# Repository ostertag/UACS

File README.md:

# UACS
University Access Controll System

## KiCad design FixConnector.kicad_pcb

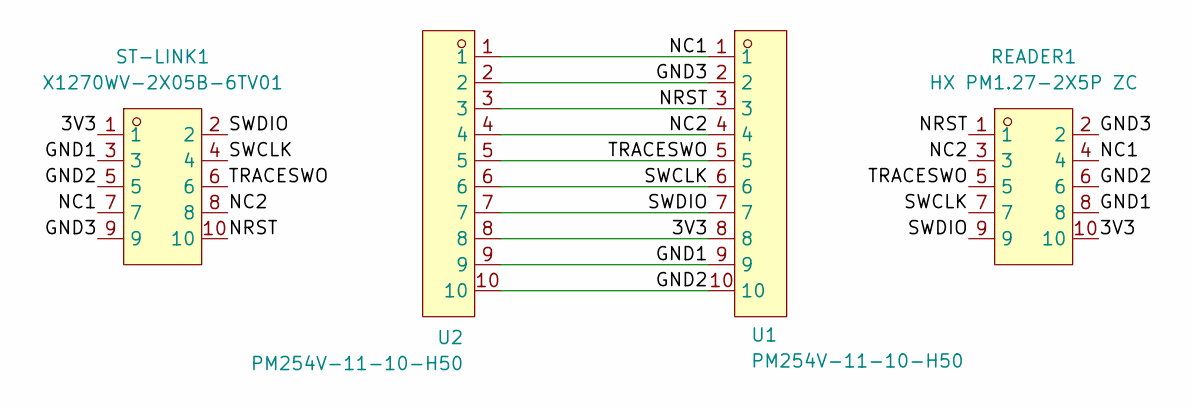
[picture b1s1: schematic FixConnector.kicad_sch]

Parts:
READER1: HX PM1.27-2X5P ZC; HDR-TH_10P-P1.27-V-F-R2-C5-S1.27; MPN HX PM1.27-2x5P ZC; LCSC Part C22438129
ST-LINK1: X1270WV-2X05B-6TV01; IDC-TH_10P-P1.27-X1270WV-2X05A-6TV01; MPN X1270WV-2x05B-9TV01; LCSC Part C2962225
U1, U2: PM254V-11-10-H50; HDR-TH_10P-P2.54-V-F-4; MPN PM254V-11-10-H50; LCSC Part C55218824

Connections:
/3V3: READER1.10, ST-LINK1.1, U1.8, U2.8
/GND1: READER1.8, ST-LINK1.3, U1.9, U2.9
/GND2: READER1.6, ST-LINK1.5, U1.10, U2.10
/GND3: READER1.2, ST-LINK1.9, U1.2, U2.2
/NC1: READER1.4, ST-LINK1.7, U1.1, U2.1
/NC2: READER1.3, ST-LINK1.8, U1.4, U2.4
/NRST: READER1.1, ST-LINK1.10, U1.3, U2.3
/SWCLK: READER1.7, ST-LINK1.4, U1.6, U2.6
/SWDIO: READER1.9, ST-LINK1.2, U1.7, U2.7
/TRACESWO: READER1.5, ST-LINK1.6, U1.5, U2.5

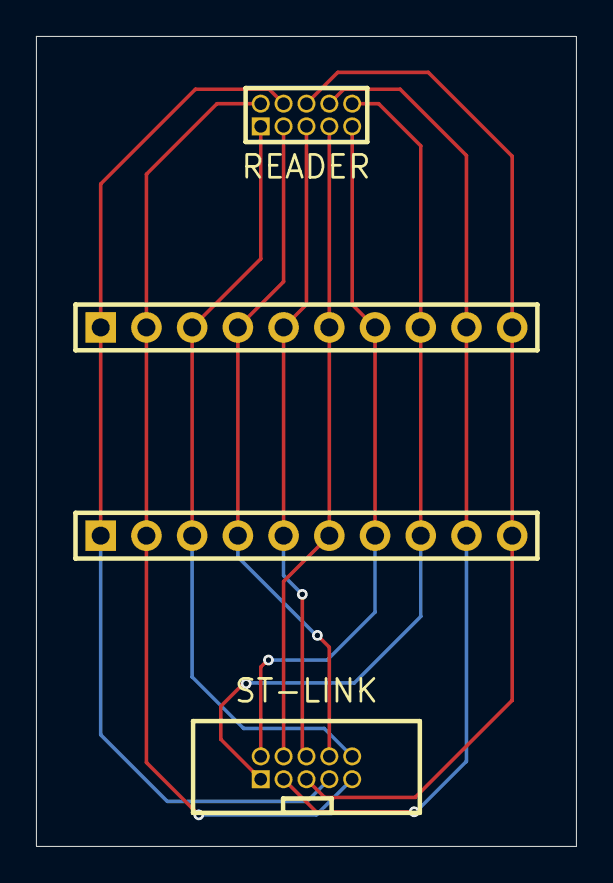
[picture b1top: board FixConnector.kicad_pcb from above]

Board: 2 copper layers, 30.0 x 45.0 mm, 4 parts (0 on the bottom side), 10 nets.

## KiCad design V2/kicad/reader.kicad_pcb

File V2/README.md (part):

# Chapter 1 — System Overview

## Project: UACS (RFID Audio CAN Node)

**Repository:** https://github.com/ostertag/UACS  
**Microcontroller:** STM32H523CET6 (Arm Cortex-M33, LQFP-48)  
**EDA tools:** KiCad (schematic + PCB), STM32CubeMX (pin/peripheral assignment)  
**Debug hardware:** STLINK-V3PWR  
**Component sourcing:** LCSC / JLCPCB

## Introduction

UACS is a custom-designed printed circuit board that integrates contactless RFID reading, audio feedback through a loudspeaker, CAN FD communication, and SD-card audio storage, built around an STM32H523CET6 microcontroller. The board communicates over a CAN FD link, carried over standard RJ45/Cat5 cabling, to a host computer (a Raspberry Pi).

The STM32H523xx is a high-performance microcontroller built on the Arm Cortex-M33 32-bit core, operating at up to 250 MHz, with a single-precision FPU and TrustZone security extension. *[1]*

## System Architecture

The system is a single-board reader node whose main functional blocks are:

- **Microcontroller** — STM32H523CET6 (Cortex-M33, 250 MHz, LQFP-48), central coordinator of all peripherals.
- **RFID reader** — RC522 module (NXP MFRC522), reads ISO/IEC 14443 A / MIFARE cards and tags over SPI.
- **Audio amplifier** — MAX98357A, digital Class D amplifier with I²S input; drives the loudspeaker directly.
- **SD card** — micro-SD slot for audio file storage, connected over SPI.
- **CAN FD transceiver** — TCAN1057A, links the board to the host over Cat5/RJ45 cabling.
- **Power supply** — dual 5 V input (USB-C and RJ45), stepped down to 3.3 V by an MCP16301H buck converter.
- **USB-C interface** — USB 2.0 full-speed device, used for firmware flashing (DFU) and debugging.
- **Indicator LEDs** — two dual-colour (red/green) SMD LEDs for user feedback.

## Scope and Goal of This Work

This work continues the UACS project previously developed in the Deadlock project series. *[predecessor]* The principal goal is a thoroughly documented hardware design that can be reliably reproduced. In particular:

- **Reproducibility** — every component value is either calculated from first principles or traced to a specific datasheet reference, so the design can be rebuilt without reliance on undocumented institutional knowledge.
- **Availability** — components are sourced from LCSC/JLCPCB and selected for availability, good documentation, and competitive cost.
- **Robustness** — the dual power input, remote reset, and remote bootloader-entry capability allow firmware updates and recovery without physical access to a deployed board.

> **Note on references.** Inline citations use italic bracketed numbers, e.g.  *[1]*, referring to the numbered list at the end of the document. References 1–11 are component datasheets; 12–23 are technical literature.

---

# Chapter 2 — Design and Assembly of the UACS PCB

The UACS reader is a printed circuit board on which an STM32H523CET6 microcontroller, an RFID front-end module, an I²S audio amplifier, a micro-SD slot, a CAN FD transceiver, and associated connectors are assembled. User feedback is provided by two dual-colour LEDs. The board can be powered either from a USB-C connector or from the RJ45 CAN cable.

## 2.1 Microcontroller — STM32H523CET6

The STM32H523CET6 is the central controller of the board. It is supplied in an LQFP-48 package and runs the Cortex-M33 core at 250 MHz. *[1]* All peripheral communication — SPI, I²S, FDCAN, and USB — is handled by this device.

### 2.1.1 Debug Interface (SWD)

The board exposes a 10-pin 1.27 mm-pitch Cortex debug connector (SWD1), driven by an STLINK-V3PWR probe.

The STM32H523 supports both JTAG and Serial Wire Debug (SWD), as well as the Embedded Trace Macrocell (ETM). *[1]* SWD was selected over JTAG because it reduces the debug interface to two active signals — SWDIO and SWCLK — while providing equivalent core-debug and memory-access capability to the higher-pin-count JTAG interface. *[12][13]* On a pin-constrained LQFP-48 device, freeing the JTAG pins (TDI, TDO, nTRST) for other functions is a meaningful saving, and SWD is the conventional default for Cortex-M bring-up. *[13]*

The Serial Wire Output trace pin (TRACESWO) is brought out on PB3, enabling single-wire instrumentation trace (printf-style debug output) without consuming a UART peripheral. The connector follows the standard 10-pin 1.27 mm Cortex-debug pinout, which balances size against reliability. *[13]*

The STLINK-V3PWR probe as we already had it available. *[4]*

### 2.1.2 Reset Circuit

The NRST line is shared between three reset sources: the on-board push button (RESET1), the remote reset line carried over the RJ45 connector (Section 2.4.2), and the STLINK debug probe. If software reset over SWD fails, the probe can still assert NRST to force a hardware reset. *[13]*

#### Resistor R5

A 10 kΩ pull-up resistor holds the NRST line high during normal operation. Without it the line would float and could trigger spurious resets from noise.

#### Capacitor C3

A 100 nF capacitor from NRST to GND provides debounce for the mechanical reset button and protection against parasitic resets. ST explicitly recommends an external capacitor on NRST for exactly this purpose. *[1]*

### 2.1.3 BOOT0 Circuit

BOOT0 selects whether the MCU starts from user flash (normal operation) or from the embedded system bootloader. The STM32H523 embedded bootloader, located in system memory and programmed by ST during production, can reprogram the flash over USART, I²C, I³C, SPI, FDCAN, or USB-FS (via DFU). *[1]* On UACS, USB-FS DFU is the relevant path (Section 2.6).

BOOT0 is additionally exposed on the RJ45 connector (Section 2.4.2), so the bootloader can be entered remotely without physical access to the board.

#### Resistor R6

A 10 kΩ pull-down resistor holds BOOT0 low during normal operation. With BOOT0 low, the device boots from user flash at address 0x0800 0000. *[1]*

#### Resistor R7

A 10 kΩ series resistor is placed between the R6 junction and the BOOT1 switch to limit current and provide isolation between the pull-down and the switch.

#### Switch BOOT1

An SPDT switch that selects GND (normal boot) or 3.3 V (bootloader entry). Connecting BOOT0 to 3.3 V causes the MCU to enter the embedded system bootloader on the next reset.

### 2.1.4 Crystal Oscillator

A 16 MHz crystal (Y1, SMD3225-4P, 10 pF load) provides the high-speed external (HSE) clock. The STM32H523 supports a 4–50 MHz HSE oscillator. *[1]* Although the device has an internal 64 MHz HSI oscillator, an external crystal is used because the USB and CAN peripherals require a more accurate and stable time base than the internal RC oscillator can guarantee. The USB full-speed interface has particularly tight frequency-tolerance requirements.

No 32.768 kHz crystal is fitted; the LSE pins (PC14/PC15) are left unconnected and configured in Analog mode.

#### Capacitors C1 and C2

Per the AN2867 oscillator load model *[24]*, the two external capacitors $C_{L1}$ and $C_{L2}$ together with PCB stray capacitance $C_S$ must equal the crystal's specified load $C_L$:

$$C_L = \frac{C_{L1} \cdot C_{L2}}{C_{L1} + C_{L2}} + C_S$$

Placing identical capacitors on both sides ($C_{L1} = C_{L2} = C$) simplifies this to $C = 2(C_L - C_S)$. With $C_L = 10\,\text{pF}$ and $C_S = 5\,\text{pF}$ (AN2867 typical range: 2–7 pF):

$$C = 2\,(10 - 5) = 10\,\text{pF}$$

Two 10 pF C0G capacitors are therefore placed to GND, one on each side of the crystal. C0G (Class 1) dielectric is used because its capacitance is essentially independent of temperature and applied voltage — typically within ±30 ppm/°C — which is important for a stable oscillator load. *[19][20]*

### 2.1.5 VCAP — Internal Regulator Capacitors

The STM32H5 family integrates an LDO voltage regulator (nominally 3.3 V → 1.2 V core) that requires external stabilisation capacitors on its VCAP pin(s). *[1]* The datasheet specifies this requirement explicitly in Section 5.3.2, "VCAP external capacitor". *[1]*

#### Capacitors C14 and C15

Two 2.2 µF capacitors, one per VCAP pin, are placed to GND. These are mandated by the datasheet for the internal regulator's stability and are not interchangeable with generic decoupling — the value and placement are part of the regulator's stability requirement.

### 2.1.6 Power Pins and Decoupling

The STM32H523 uses several supply domains: the main VDD digital supply, an analog supply (VDDA), a USB supply domain, and the VBAT backup domain. *[1]*

- **VDD** — supplied from +3.3 V; decoupled with C8–C11 (100 nF each) for high-frequency bypass, plus C12 (10 µF) for bulk capacitance.
- **VDDA** — analog supply, filtered from the 3.3 V rail through the VDDA filter (Section 2.3.3).
- **VBAT** — tied to the 3.3 V rail, since no backup battery is used.
- **VSS / VSSA** — ground.

### 2.1.7 RFID Reader — RC522 Module (MFRC522)

The RFID front end is an RC522 module based on the NXP MFRC522 IC, mounted on an 8-pin 2.54 mm socket (RC1) and connected to the MCU over SPI.

The RC522 module was selected because it was used in the predecessor project, allowing existing experience and firmware to be carried over. The MFRC522 is a 13.56 MHz reader/writer IC supporting the ISO/IEC 14443 A / MIFARE protocol family — MIFARE Mini, 1K, 4K, Ultralight, DESFire EV1, MIFARE Plus, and NTAG — with a host SPI interface running up to 10 Mbit/s. *[3]*

**Interface signals:**

- **SPI** — shares SPI1 with the SD card (Section 2.2); chip select is software-controlled on PB14 (RFID_SS), active low.
- **RST (PB10)** — the MCU drives the module's NRSTPD pin as a push-pull output. The pin defaults high at boot so the reader starts in normal operation; driving it low triggers a hard reset/power-down of the module. *[3]*
- **IRQ (PB13)** — the module's interrupt output drives EXTI13, configured for falling-edge interrupts, enabling interrupt-driven card detection rather than polling.

On the MFRC522, the IRQ pin is open-drain and active-low by default, *[3]* which matches the MCU's falling-edge EXTI configuration; only an MCU-side internal pull-up is required on PB13, with no external resistor. The MFRC522's CommIEnReg register must be configured in firmware to enable interrupt propagation to the IRQ pin. *[3]*

#### Capacitor C21

A 10 µF local bypass capacitor is placed on the module VCC pin. VCC connects directly to the 3.3 V rail. (PB12 is left unconnected; an earlier plan to use it for switched module power was dropped, since a single GPIO cannot source the MFRC522's worst-case current.)

---

## 2.2 SD Card — MLD-TF PUSH-H18

The micro-SD slot (U3) stores the audio files played back through the amplifier.

SPI was chosen over SDMMC for three reasons: the application does not require SDMMC's higher throughput; SPI was already in use for the RFID reader, reducing the number of active interfaces and occupied pins; and while this STM32 series supports SDMMC, it is only available on larger packages.

The SD card shares SPI1 with the RC522 reader, with its own software chip select on PB0 (SD_SS). In SPI mode, the card's CD/DAT3 pin (slot pin 2) functions as the active-low chip select; this is confirmed by the slot's pin table, which labels pin 2 as CD/DAT3 with I/O type PP. *[8]*

The MLD-TF PUSH-H18 uses a push-push ejection mechanism (card ejects on the second press); the card-detect switch is a separate mechanical contact from the signal pins. *[8]*

#### Card Detect — PB1

The slot's dedicated card-detect mechanical contact drives PB1 (SD_DETECTED) as a GPIO input, allowing the firmware to detect card insertion and removal.

#### Resistors R2 and R3

Two 10 kΩ pull-up resistors are placed to 3.3 V on the DAT1 line (R2) and the DAT2 line (R3). In SPI mode both of these data lines are unused; the pull-ups keep them at a defined high level rather than floating.

---

## 2.3 Power Supply

### 2.3.1 Architecture

The board accepts power from two independent 5 V sources, diode-OR-ed onto a common +5 V rail and then stepped down to 3.3 V by a buck converter.

| Source | OR-ing diode | ESD protection |
|--------|--------------|----------------|
| USB-C VBUS | D8 (PMEG2010ER) | D7 (PESD5V0U1BA,115) |
| RJ45 pair (brown) | D1 (PMEG2010ER) | D2 (PESD5V0U1BA,115) |

The two inputs serve different operational scenarios. The RJ45 input is the primary supply during normal deployment, where the board is powered from the CAN cabling infrastructure. The USB-C input is used during development and programming, when the board is connected to a PC without the full CAN harness. Diode OR-ing lets both sources be connected simultaneously without back-feeding. Each TVS diode is placed as close as possible to its respective input connector for effective clamping. *[10]*

### 2.3.2 Buck Converter — MCP16301H

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
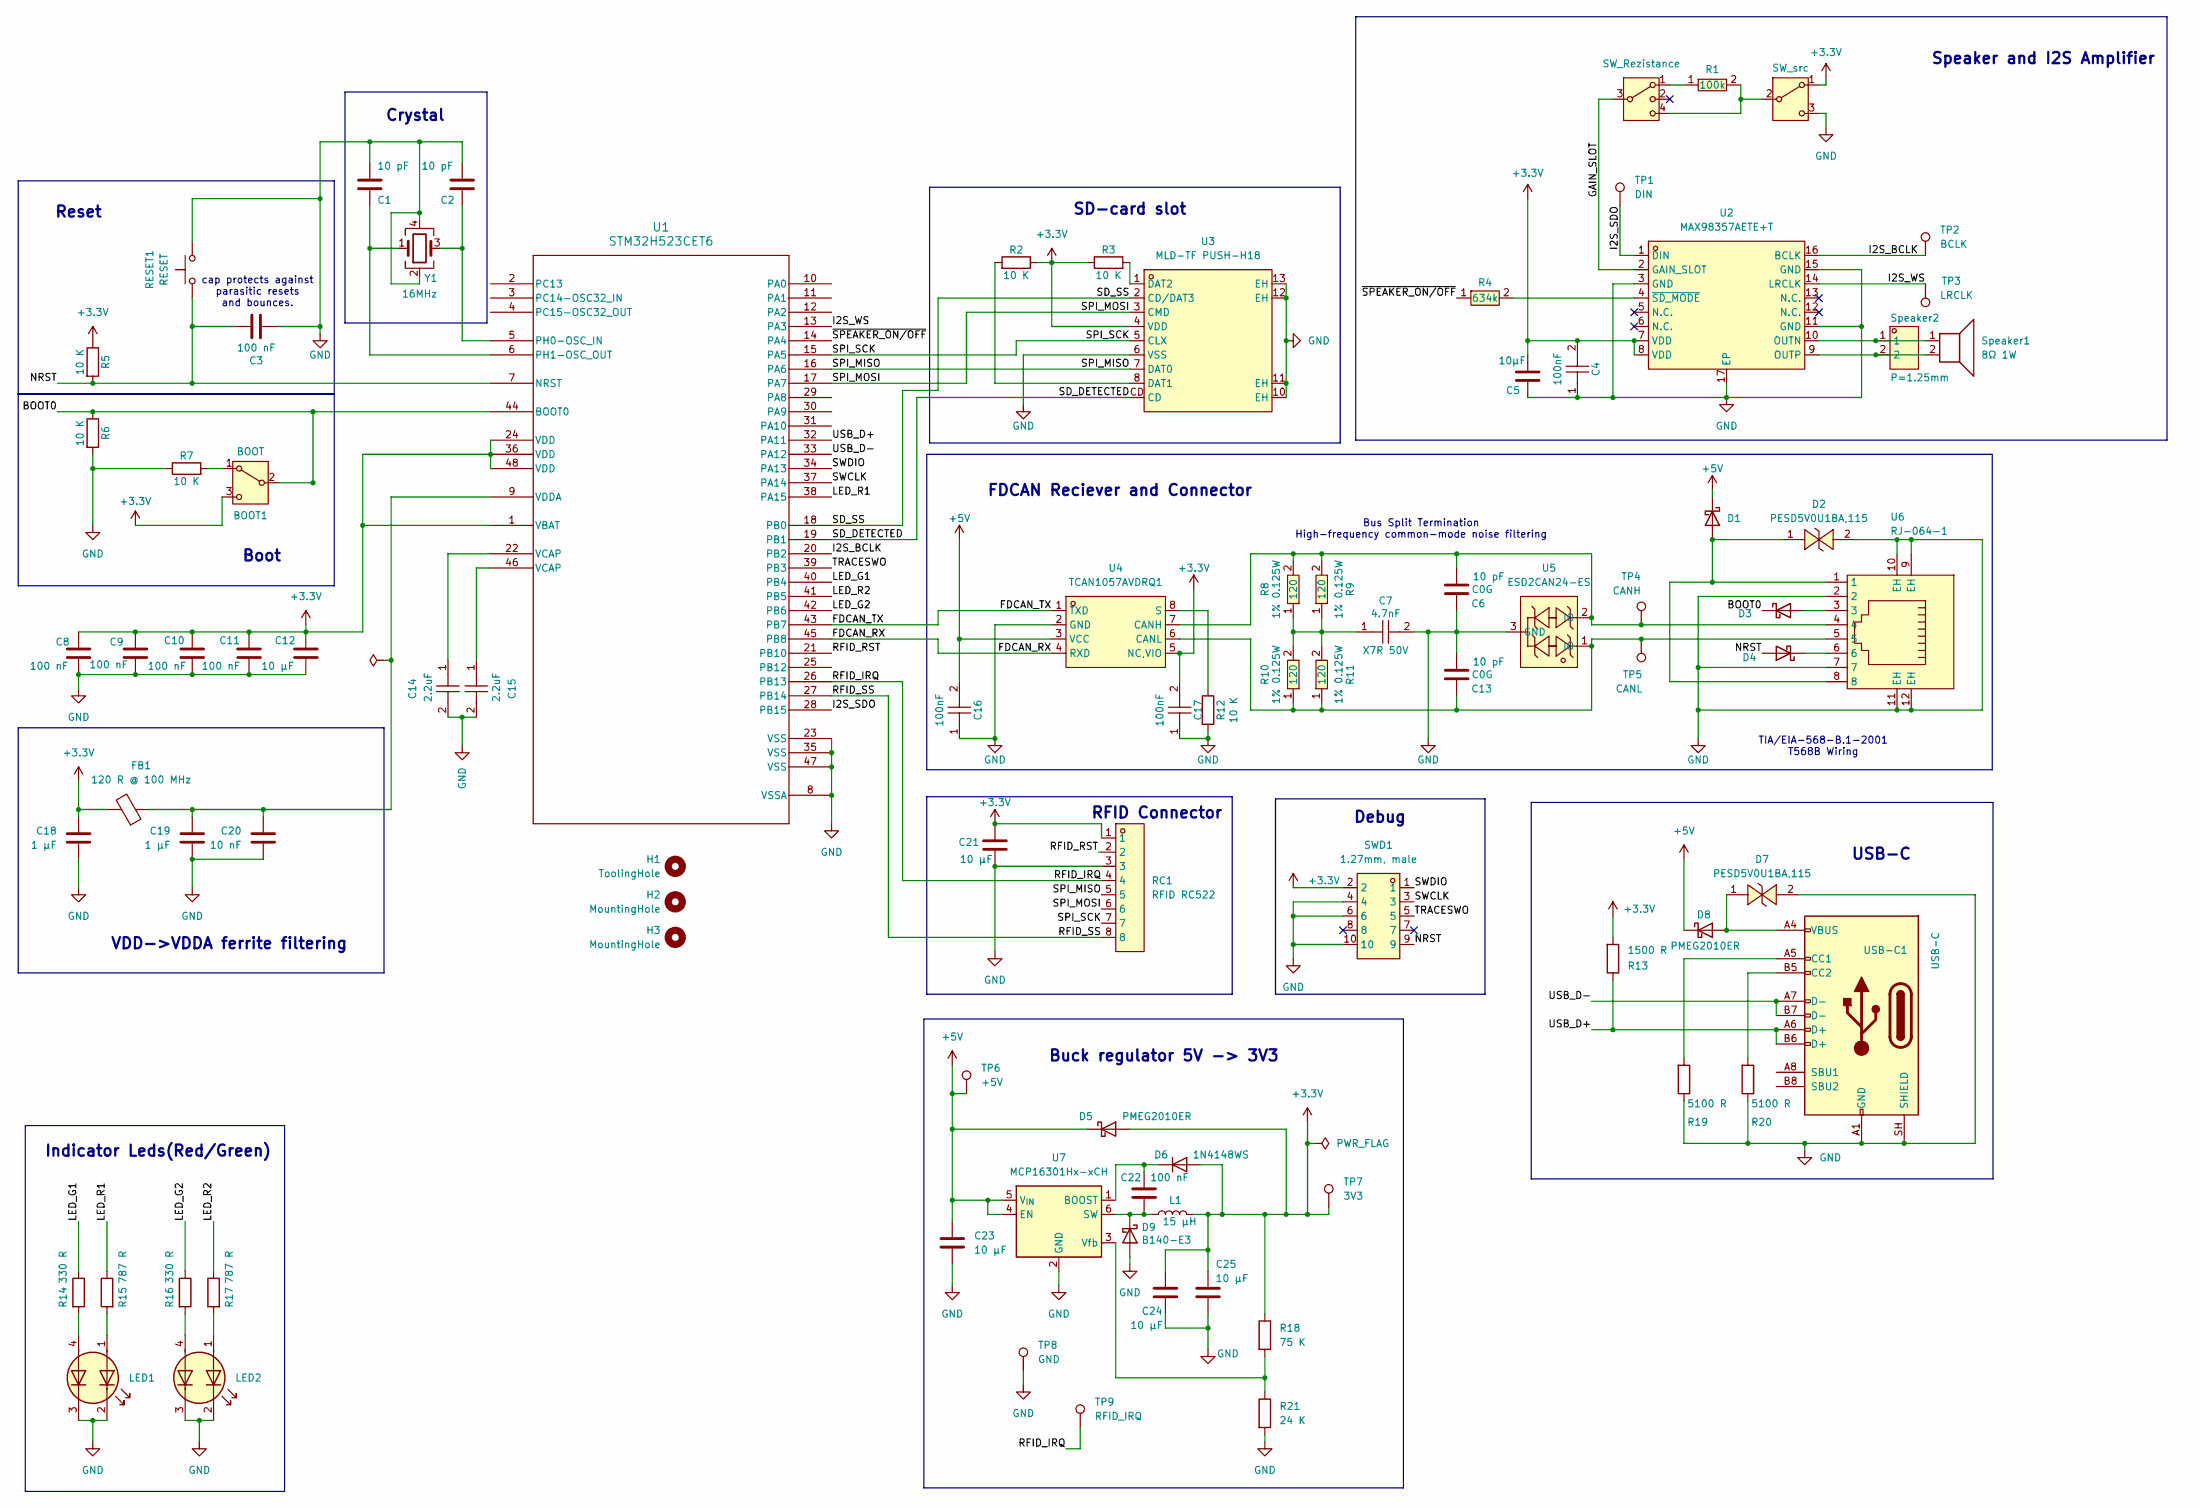
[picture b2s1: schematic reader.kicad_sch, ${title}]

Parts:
BOOT1: BOOT; SW_SPDT_PCM12; LCSC C109335
C1, C2, C6, C13: 10 pF; C_0402_1005Metric; LCSC C32949
C3, C8, C9, C10, C11, C22: 100 nF; C_0402_1005Metric; LCSC C1525
C4, C16, C17: CC0603KRX7R9BB104; C0603; MPN CC0603KRX7R9BB104; LCSC Part C14663
C5: 10µF; C_0603_1608Metric; LCSC C96446
C7: 4.7nF; C0603; MPN CC0603JRX7R9BB472; LCSC Part C115060
C12, C21, C23, C24, C25: 10 µF; C_0603_1608Metric; LCSC C96446
C14, C15: GRM155C80J225KE95D; C0402; MPN GRM155C80J225KE95D; LCSC Part C521077
C18, C19: 1 µF; C_0402_1005Metric; LCSC C52923
C20: 10 nF; C_0402_1005Metric; LCSC C15195
D1, D3, D4, D5, D8: PMEG2010ER; Nexperia_CFP3_SOD-123W; LCSC C82288
D2, D7: PESD5V0U1BA,115; SOD-323_L1.8-W1.3-LS2.5-BI; MPN PESD5V0U1BA,115; LCSC Part C552574
D6: 1N4148WS; D_SOD-323; LCSC C2128
D9: B140-E3; D_SMA; LCSC C968568
FB1: 120 R @ 100 MHz; L_0603_1608Metric; LCSC C2661467
H1: ToolingHole; ToolingHole_1.152mm
H2, H3: MountingHole; ToolingHole_1.152mm
L1: 15 µH; L_Coilcraft_LPS3010; LCSC C520285
LED1, LED2: APHBM2012LSURKZGKC; LED_Kingbright_APHBM2012_2x1.25mm; LCSC C6465979
R1: 0603WAF1003T5E; R0603; MPN 0603WAF1003T5E; LCSC Part C25803
R2, R3, R5, R6, R7, R12: 10 K; R_0603_1608Metric; LCSC C25804
R4: 0805W8F1501T5E; R0805; MPN 0805W8F1501T5E; LCSC Part C4310
R8, R9, R10, R11: 120; R0805; MPN CL0805FN120RP; LCSC Part C17437
R13: 1500 R; R_0402_1005Metric; LCSC C25867
R14, R16: 330 R; R_0402_1005Metric; LCSC C25104
R15, R17: 787 R; R_0402_1005Metric; LCSC C4109
R18: 75 K; R_0603_1608Metric; LCSC C23242
R19, R20: 5100 R; R_0402_1005Metric; LCSC C25905
R21: 24 K; R_0603_1608Metric; LCSC C23352
RC1: RFID RC522; PinSocket_1x08_P2.54mm_Vertical; MPN HX PM2.54-1x8P ZC H11; LCSC Part C41427523
RESET1: RESET; SW_PUSH_6mm; LCSC C2889001
SW1: SW_Rezistance; SW-SMD_SSSS812201; LCSC Part C160878
SW2: SW_src; SW_SPDT_PCM12; LCSC C109335
SWD1: 1.27mm, male; IDC-TH_10P-P1.27-X1270WV-2X05A-6TV01; MPN X1270WV-2x05B-9TV01; LCSC Part C2962225
Speaker1: 8Ω 1W; LCSC C530539
Speaker2: P=1.25mm; CONN-TH_0530470210; MPN 530470210; LCSC Part C114130
TP1: DIN; TestPoint_Drill-1mm
TP2: BCLK; TestPoint_Drill-1mm
TP3: LRCLK; TestPoint_Drill-1mm
TP4: CANH; TestPoint_Drill-1mm
TP5: CANL; TestPoint_Drill-1mm
TP6: +5V; TestPoint_Drill-1mm
TP7: 3V3; TestPoint_Drill-1mm
TP8: GND; TestPoint_Drill-1mm
TP9: RFID_IRQ; TestPoint_Drill-1mm
U1: STM32H523CET6; LQFP48_STM
U2: MAX98357AETE+T; TQFN-16_L3.0-W3.0-P0.50-BL-EP1.5; MPN MAX98357AETE+T; LCSC Part C910544
U3: MLD-TF PUSH-H18; SD-SMD_MLD-TF-PUSH-H18; MPN MLD-TF PUSH-H18; LCSC Part C52750848
U4: TCAN1057AVDRQ1; SOIC-8_L4.9-W3.9-P1.27-LS6.0-BL; MPN TCAN1057AVDRQ1; LCSC Part C3235000
U5: ESD2CAN24-ES; SOT-23-3_L2.9-W1.3-P1.90-LS2.4-BR; MPN ESD2CAN24-ES; LCSC Part C19170841
U6: RJ-064-1; CONN-SMD_RJ-064; MPN RJ-064-1; LCSC Part C7205199
U7: MCP16301Hx-xCH; SOT-23-6; LCSC C511272
USB-C1: USB-C; USB_C_Receptacle_GCT_USB4105-xx-A_16P_TopMnt_Horizontal; LCSC C2765186
Y1: 16MHz; Crystal_SMD_3225-4Pin_3.2x2.5mm; LCSC C13738

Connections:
+3.3V: BOOT1.3 (C), C4.2, C5.2, C8.1, C9.1, C10.1, C11.1, C12.1, C17.2, C18.1, C21.1, C24.1, C25.1, D5.2 (A), D6.2 (A), FB1.2, L1.2, R2.1, R3.1, R5.1, R13.2, R18.1, RC1.1, SW2.1 (A), SWD1.2, TP7.1 (1_1), U1.1 (VBAT), U1.24 (VDD), U1.36 (VDD), U1.48 (VDD), U2.7 (VDD), U2.8 (VDD), U3.4 (VDD), U4.5 (NC,VIO); also elsewhere on the board
+5V: C16.2, C23.1, D1.1 (K), D5.1 (K), D8.1 (K), TP6.1 (1_1), U4.3 (VCC), U7.4 (EN), U7.5 (V_{IN})
/BOOT0: BOOT1.2 (B), D3.1 (K), R6.1, U1.44 (BOOT0)
/FDCAN_RX: U1.45 (PB8), U4.4 (RXD)
/FDCAN_TX: U1.43 (PB7), U4.1 (TXD)
/GAIN_SLOT: SW1.3, U2.2 (GAIN_SLOT)
/I2S_BCLK: TP2.1 (1_1), U1.20 (PB2), U2.16 (BCLK)
/I2S_SDO: TP1.1 (1_1), U1.28 (PB15), U2.1 (DIN)
/I2S_WS: TP3.1 (1_1), U1.13 (PA3), U2.14 (LRCLK)
/LED_G1: R14.1, U1.40 (PB4)
/LED_G2: R16.1, U1.42 (PB6)
/LED_R1: R15.1, U1.38 (PA15)
/LED_R2: R17.1, U1.41 (PB5)
/NRST: C3.1, D4.2 (A), R5.2, RESET1.1, SWD1.9, U1.7 (NRST); also elsewhere on the board
/RFID_IRQ: RC1.4, TP9.1 (1_1), U1.26 (PB13)
/RFID_RST: RC1.2, U1.21 (PB10)
/RFID_SS: RC1.8, U1.27 (PB14)
/SD_DETECTED: U1.19 (PB1), U3.CD
/SD_SS: U1.18 (PB0), U3.2 (CD/DAT3)
/SPI_MISO: RC1.5, U1.16 (PA6), U3.7 (DAT0)
/SPI_MOSI: RC1.6, U1.17 (PA7), U3.3 (CMD)
/SPI_SCK: RC1.7, U1.15 (PA5), U3.5 (CLX)
/SWCLK: SWD1.3, U1.37 (PA14); also elsewhere on the board
/SWDIO: SWD1.1, U1.34 (PA13); also elsewhere on the board
/TRACESWO: SWD1.5, U1.39 (PB3); also elsewhere on the board
/USB_D+: R13.1, U1.32 (PA11), USB-C1.A6 (D+), USB-C1.B6 (D+)
/USB_D-: U1.33 (PA12), USB-C1.A7 (D-), USB-C1.B7 (D-)
/~SPEAKER_ON/OFF: R4.1, U1.14 (PA4)
GND: C1.2, C2.2, C3.2, C4.1, C5.1, C6.1, C7.2, C8.2, C9.2, C10.2, C11.2, C12.2, C13.2, C14.2, C15.2, C16.1, C17.1, C18.2, C19.2, C20.2, C21.2, C23.2, C24.2, C25.2, D2.2, D7.2, D9.2 (A), LED1.2 (K1), LED1.3 (K2), LED2.2 (K1), LED2.3 (K2), R6.2, R7.1, R12.2, R19.1, R20.1, R21.2, RC1.3, RESET1.2, SW2.3 (C), SWD1.4, SWD1.6, SWD1.10, TP8.1 (1_1), U1.8 (VSSA), U1.23 (VSS), U1.35 (VSS), U1.47 (VSS), U2.3 (GND), U2.11 (GND), U2.15 (GND), U2.17 (EP), U3.6 (VSS), U3.10 (EH), U3.11 (EH), U3.12 (EH), U3.13 (EH), U4.2 (GND), U5.3 (GND), U6.2, U6.7, U6.9 (EH), U6.10 (EH), U6.11 (EH), U6.12 (EH), U7.2 (GND), USB-C1.A1 (GND), USB-C1.A12 (GND), USB-C1.B1 (GND), USB-C1.B12 (GND), USB-C1.SH (SHIELD), Y1.2, Y1.4; also elsewhere on the board
unnamed: BOOT1.1 (A), R7.2
unnamed: C7.1, R8.1, R9.1, R10.2, R11.2
unnamed: C14.1, U1.22 (VCAP)
unnamed: C15.1, U1.46 (VCAP)
unnamed: D1.2 (A), D2.1, U6.1, U6.8
unnamed: D3.2 (A), U6.3
unnamed: D4.1 (K), U6.6
unnamed: C22.1, D6.1 (K), U7.1 (BOOST)
unnamed: D7.1, D8.2 (A), USB-C1.A4 (VBUS), USB-C1.A9 (VBUS), USB-C1.B4 (VBUS), USB-C1.B9 (VBUS)
unnamed: C22.2, D9.1 (K), L1.1, U7.6 (SW)
unnamed: LED1.1 (A1), R15.2
unnamed: LED1.4 (A2), R14.2
unnamed: LED2.1 (A1), R17.2
unnamed: LED2.4 (A2), R16.2
unnamed: R1.1, SW1.1
unnamed: R1.2, SW1.4, SW2.2 (B)
unnamed: C2.1, U1.5 (PH0-OSC_IN), Y1.3
unnamed: C1.1, U1.6 (PH1-OSC_OUT), Y1.1
unnamed: C19.1, C20.1, FB1.1, U1.9 (VDDA)
unnamed: Speaker1.1, Speaker2.1, U2.10 (OUTN)
unnamed: Speaker1.2, Speaker2.2, U2.9 (OUTP)
unnamed: R4.2, U2.4 (~SD_MODE)
unnamed: R2.2, U3.8 (DAT1)
unnamed: R3.2, U3.1 (DAT2)
unnamed: C6.2, R8.2, R9.2, TP4.1 (1_1), U4.7 (CANH), U5.2 (IO), U6.4
unnamed: C13.1, R10.1, R11.1, TP5.1 (1_1), U4.6 (CANL), U5.1 (IO), U6.5
unnamed: R12.1, U4.8 (S)
unnamed: R18.2, R21.1, U7.3 (Vfb)
unnamed: R19.2, USB-C1.A5 (CC1)
unnamed: R20.2, USB-C1.B5 (CC2)

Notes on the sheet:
VDD->VDDA ferrite filtering
Debug
Bus Split Termination High-frequency common-mode noise filtering
RFID Connector
SD-card slot
cap protects against parasitic resets and bounces.
USB-C
TIA/EIA-568-B.1-2001 T568B Wiring
Speaker and I2S Amplifier
Indicator Leds(Red/Green)
Crystal
Buck regulator 5V -> 3V3
Reset
FDCAN Reciever and Connector
Boot

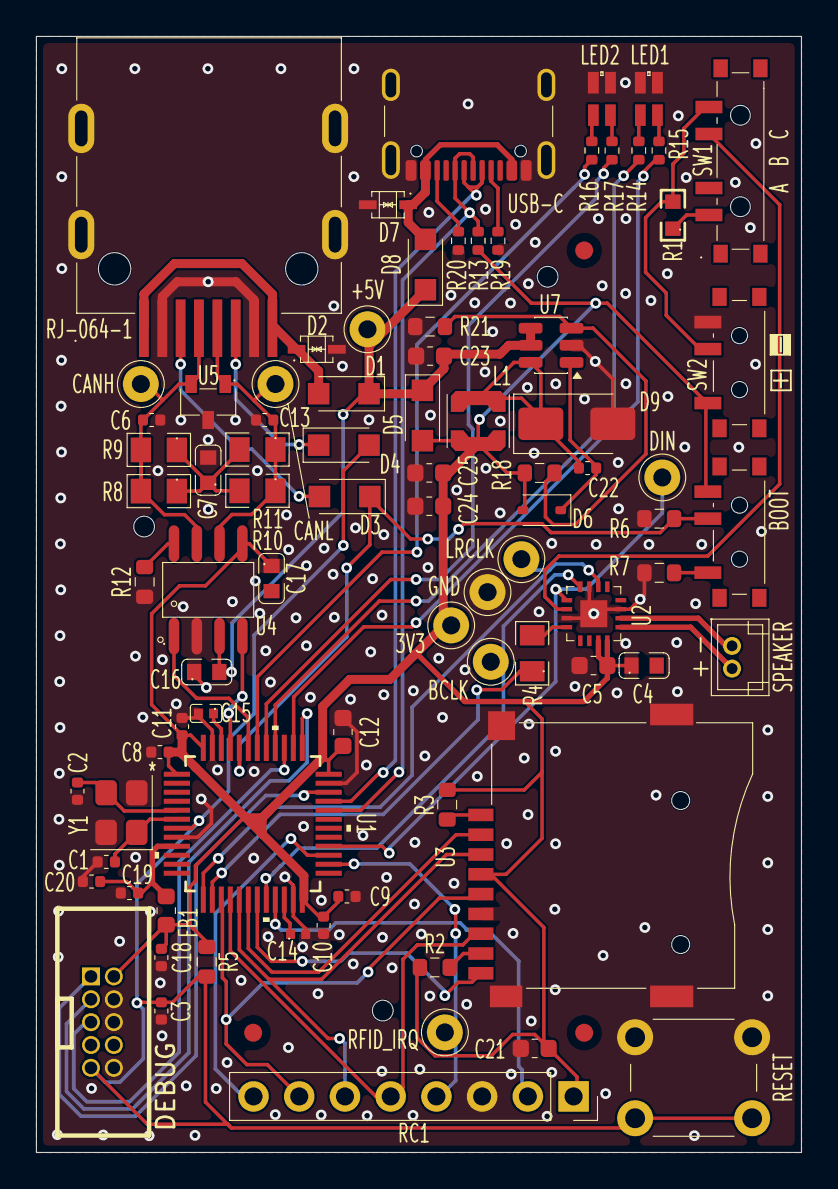
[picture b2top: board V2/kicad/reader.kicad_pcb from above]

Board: 2 copper layers, 42.5 x 62.0 mm, 87 parts (0 on the bottom side), 59 nets.

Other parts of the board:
DEBUG: 1.27mm, male; IDC-TH_10P-P1.27-X1270WV-2X05A-6TV01

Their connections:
+3.3V: DEBUG.2; also elsewhere on the board
/NRST: DEBUG.9; also elsewhere on the board
/SWCLK: DEBUG.3; also elsewhere on the board
/SWDIO: DEBUG.1; also elsewhere on the board
/TRACESWO: DEBUG.5; also elsewhere on the board
GND: DEBUG.4, DEBUG.6, DEBUG.10; also elsewhere on the board

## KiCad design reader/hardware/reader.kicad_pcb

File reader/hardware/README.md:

Here is whole project from KICAD ver 9  
For production on JLCPCB site is advised to used plugin Fabrication toolkit for creating boom and plt files  
For detailed descriptions on of components, refer to [branch hardware_kozuch](https://github.com/ostertag/UACS/tree/hardwear_kozuch)

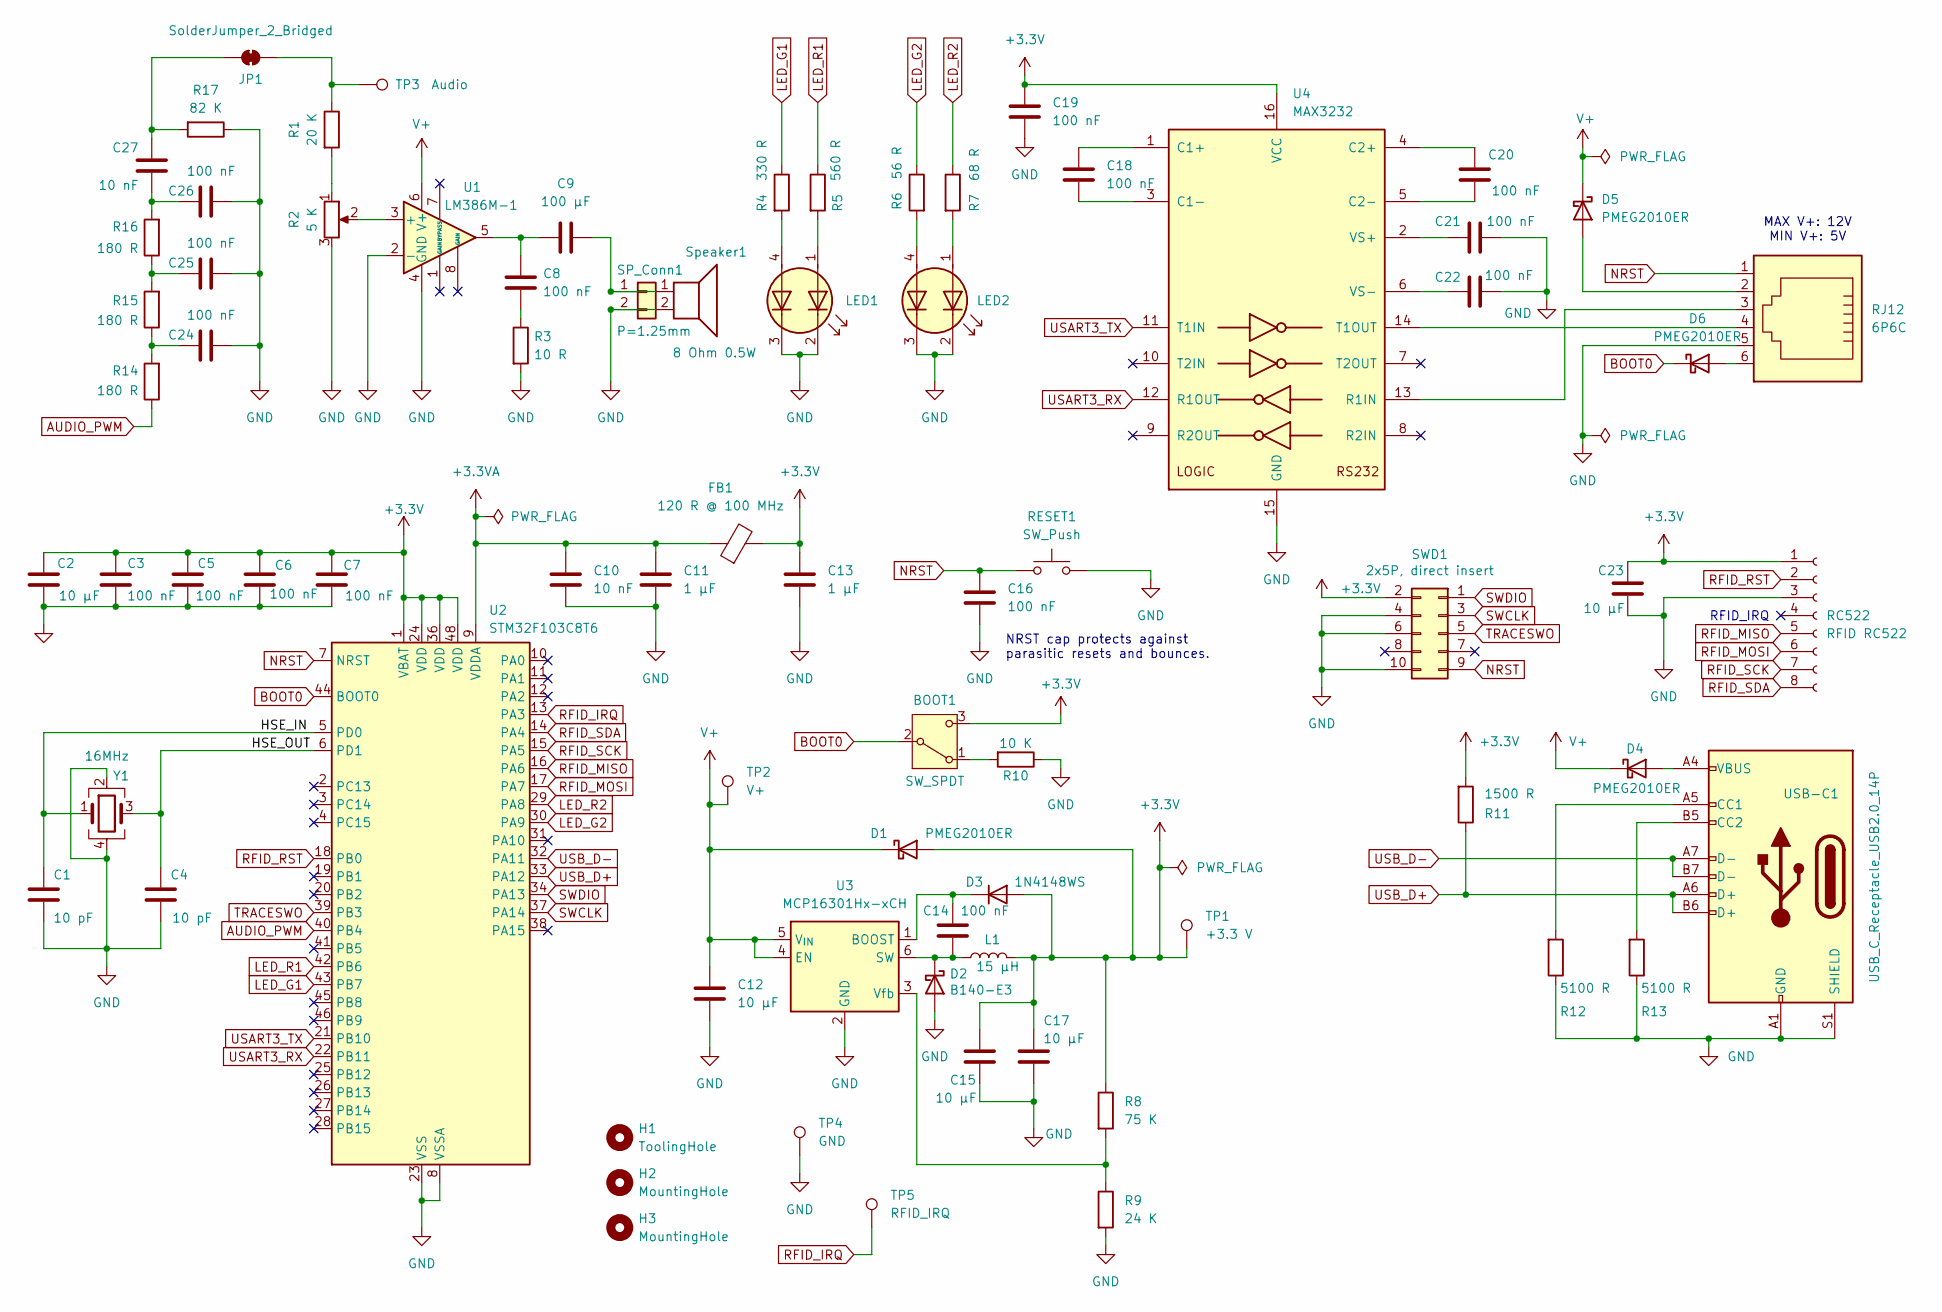
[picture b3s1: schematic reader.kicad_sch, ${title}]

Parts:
BOOT1: SW_SPDT; SW_SPDT_PCM12; LCSC C109335
C1, C4: 10 pF; C_0402_1005Metric; LCSC C32949
C2, C12, C15, C17, C23: 10 µF; C_0603_1608Metric; LCSC C96446
C3, C5, C6, C7, C8, C14, C16, C18, C19, C20, C21, C22, C24, C25, C26: 100 nF; C_0402_1005Metric; LCSC C1525
C9: 100 µF; C_1206_3216Metric; LCSC C15008
C10, C27: 10 nF; C_0402_1005Metric; LCSC C15195
C11, C13: 1 µF; C_0402_1005Metric; LCSC C52923
D1, D4, D5, D6: PMEG2010ER; Nexperia_CFP3_SOD-123W; LCSC C82288
D2: B140-E3; D_SMA; LCSC C968568
D3: 1N4148WS; D_SOD-323; LCSC C2128
FB1: 120 R @ 100 MHz; L_0603_1608Metric; LCSC C2661467
H1: ToolingHole; ToolingHole_1.152mm
H2, H3: MountingHole; ToolingHole_1.152mm
JP1: SolderJumper_2_Bridged; SolderJumper-2_P1.3mm_Bridged_RoundedPad1.0x1.5mm
L1: 15 µH; L_Coilcraft_LPS3010; LCSC C520285
LED1: APHBM2012LSURKZGKC; LED_Kingbright_APHBM2012_2x1.25mm; LCSC C6465979
LED2: APHBM2012SURKCGKC; LED_Kingbright_APHBM2012_2x1.25mm; LCSC C5553822
R1: 20 K; R_0402_1005Metric; LCSC C25765
R2: 5 K; Potentiometer_Bourns_3314J_Vertical; LCSC C58391
R3: 10 R; R_0402_1005Metric; LCSC C25077
R4: 330 R; R_0402_1005Metric; LCSC C25104
R5: 560 R; R_0603_1608Metric; LCSC C23204
R6: 56 R; R_0402_1005Metric; LCSC C25127
R7: 68 R; R_0402_1005Metric; LCSC C163455
R8: 75 K; R_0603_1608Metric; LCSC C23242
R9: 24 K; R_0603_1608Metric; LCSC C23352
R10: 10 K; R_0603_1608Metric; LCSC C25804
R11: 1500 R; R_0402_1005Metric; LCSC C25867
R12, R13: 5100 R; R_0402_1005Metric; LCSC C25905
R14, R15, R16: 180 R; R_0402_1005Metric; LCSC C102848
R17: 82 K; R_0603_1608Metric; LCSC C23254
RC522: RFID RC522; PinSocket_1x08_P2.54mm_Vertical; LCSC C27438
RESET1: SW_Push; SW_PUSH_6mm; LCSC C2889001
RJ12: 6P6C; RJ12_Amphenol_54601-x06_Horizontal; LCSC C4355015
SP_Conn1: P=1.25mm; Molex_PicoBlade_53047-0210_1x02_P1.25mm_Vertical; LCSC C114130
SWD1: 2x5P, direct insert; PinSocket_2x05_P1.27mm_Vertical; LCSC C350287
Speaker1: 8 Ohm 0.5W; LCSC C530539
TP1: +3.3 V; TestPoint_THTPad_D1.0mm_Drill0.5mm
TP2: V+; TestPoint_THTPad_D1.0mm_Drill0.5mm
TP3: Audio; TestPoint_THTPad_D1.0mm_Drill0.5mm
TP4: GND; TestPoint_THTPad_D1.0mm_Drill0.5mm
TP5: RFID_IRQ; TestPoint_THTPad_D1.0mm_Drill0.5mm
U1: LM386M-1; SOIC-8_3.9x4.9mm_P1.27mm; LCSC C5375298
U2: STM32F103C8T6; LQFP-48_7x7mm_P0.5mm; LCSC C8734
U3: MCP16301Hx-xCH; SOT-23-6; LCSC C511272
U4: MAX3232; SOIC-16_3.9x9.9mm_P1.27mm; LCSC C81661
USB-C1: USB_C_Receptacle_USB2.0_14P; USB_C_Receptacle_GCT_USB4105-xx-A_16P_TopMnt_Horizontal; LCSC C2765186
Y1: 16MHz; Crystal_SMD_3225-4Pin_3.2x2.5mm; LCSC C13738

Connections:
+3.3V: BOOT1.3 (C), C2.1, C3.1, C5.1, C6.1, C7.1, C13.1, C15.1, C17.1, C19.1, C23.1, D1.2 (A), D3.2 (A), FB1.2, L1.2, R8.1, R11.2, RC522.1, SWD1.2, TP1.1, U2.1 (VBAT), U2.24 (VDD), U2.36 (VDD), U2.48 (VDD), U4.16 (VCC)
+3.3VA: C10.1, C11.1, FB1.1, U2.9 (VDDA)
/HSE_IN: C1.1, U2.5 (PD0), Y1.1
/HSE_OUT: C4.1, U2.6 (PD1), Y1.3
AUDIO_PWM: R14.1, U2.40 (PB4)
BOOT0: BOOT1.2 (B), D6.1 (K), U2.44 (BOOT0)
GND: C1.2, C2.2, C3.2, C4.2, C5.2, C6.2, C7.2, C10.2, C11.2, C12.2, C13.2, C15.2, C16.2, C17.2, C19.2, C21.2, C22.2, C23.2, C24.2, C25.2, C26.2, D2.2 (A), LED1.2 (K1), LED1.3 (K2), LED2.2 (K1), LED2.3 (K2), R2.3, R3.2, R9.2, R10.1, R12.1, R13.1, R17.1, RC522.3, RESET1.2, RJ12.5, SP_Conn1.2, SWD1.4, SWD1.6, SWD1.10, Speaker1.2, TP4.1, U1.2 (-), U1.4 (GND), U2.8 (VSSA), U2.23 (VSS), U2.35 (VSS), U2.47 (VSS), U3.2 (GND), U4.15 (GND), USB-C1.A1 (GND), USB-C1.A12 (GND), USB-C1.B1 (GND), USB-C1.B12 (GND), USB-C1.S1 (SHIELD), Y1.2, Y1.4
LED_G1: R4.1, U2.43 (PB7)
LED_G2: R6.1, U2.30 (PA9)
LED_R1: R5.1, U2.42 (PB6)
LED_R2: R7.1, U2.29 (PA8)
NRST: C16.1, RESET1.1, RJ12.1, SWD1.9, U2.7 (NRST)
unnamed: BOOT1.1 (A), R10.2
unnamed: C8.1, C9.1, U1.5
unnamed: C8.2, R3.1
unnamed: C24.1, R14.2, R15.1
unnamed: C25.1, R15.2, R16.1
unnamed: C26.1, C27.1, R16.2
unnamed: C14.2, D2.1 (K), L1.1, U3.6 (SW)
unnamed: C14.1, D3.1 (K), U3.1 (BOOST)
unnamed: D4.2 (A), USB-C1.A4 (VBUS), USB-C1.A9 (VBUS), USB-C1.B4 (VBUS), USB-C1.B9 (VBUS)
unnamed: D5.2 (A), RJ12.2
unnamed: D6.2 (A), RJ12.6
unnamed: C27.2, JP1.1 (A), R17.2
unnamed: JP1.2 (B), R1.1, TP3.1
unnamed: LED1.1 (A1), R5.2
unnamed: LED1.4 (A2), R4.2
unnamed: LED2.1 (A1), R7.2
unnamed: LED2.4 (A2), R6.2
unnamed: R1.2, R2.1
unnamed: C9.2, SP_Conn1.1, Speaker1.1
unnamed: R2.2, U1.3 (+)
unnamed: R8.2, R9.1, U3.3 (Vfb)
unnamed: C18.1, U4.1 (C1+)
unnamed: C18.2, U4.3 (C1-)
unnamed: C20.1, U4.4 (C2+)
unnamed: C20.2, U4.5 (C2-)
unnamed: RJ12.3, U4.13 (R1IN)
unnamed: RJ12.4, U4.14 (T1OUT)
unnamed: C21.1, U4.2 (VS+)
unnamed: C22.1, U4.6 (VS-)
unnamed: R12.2, USB-C1.A5 (CC1)
unnamed: R13.2, USB-C1.B5 (CC2)
RFID_IRQ: TP5.1, U2.13 (PA3)
RFID_MISO: RC522.5, U2.16 (PA6)
RFID_MOSI: RC522.6, U2.17 (PA7)
RFID_RST: RC522.2, U2.18 (PB0)
RFID_SCK: RC522.7, U2.15 (PA5)
RFID_SDA: RC522.8, U2.14 (PA4)
SWCLK: SWD1.3, U2.37 (PA14)
SWDIO: SWD1.1, U2.34 (PA13)
TRACESWO: SWD1.5, U2.39 (PB3)
USART3_RX: U2.22 (PB11), U4.12 (R1OUT)
USART3_TX: U2.21 (PB10), U4.11 (T1IN)
USB_D+: R11.1, U2.33 (PA12), USB-C1.A6 (D+), USB-C1.B6 (D+)
USB_D-: U2.32 (PA11), USB-C1.A7 (D-), USB-C1.B7 (D-)
V+: C12.1, D1.1 (K), D4.1 (K), D5.1 (K), TP2.1, U1.6 (V+), U3.4 (EN), U3.5 (V_{IN})

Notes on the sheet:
MAX V+: 12V MIN V+: 5V
NRST cap protects against parasitic resets and bounces.
RFID_IRQ

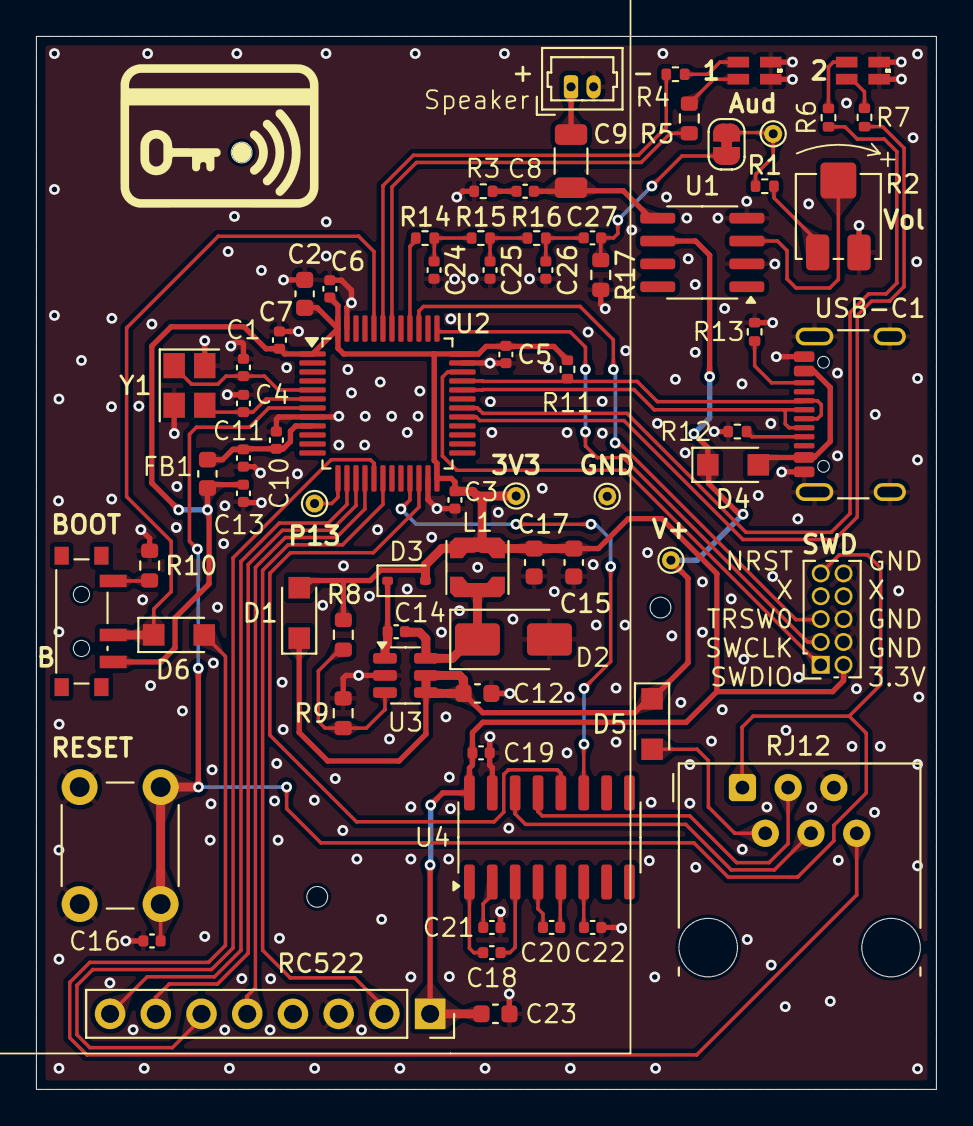
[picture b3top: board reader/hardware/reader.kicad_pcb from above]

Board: 2 copper layers, 50.0 x 58.5 mm, 75 parts (0 on the bottom side), 57 nets.

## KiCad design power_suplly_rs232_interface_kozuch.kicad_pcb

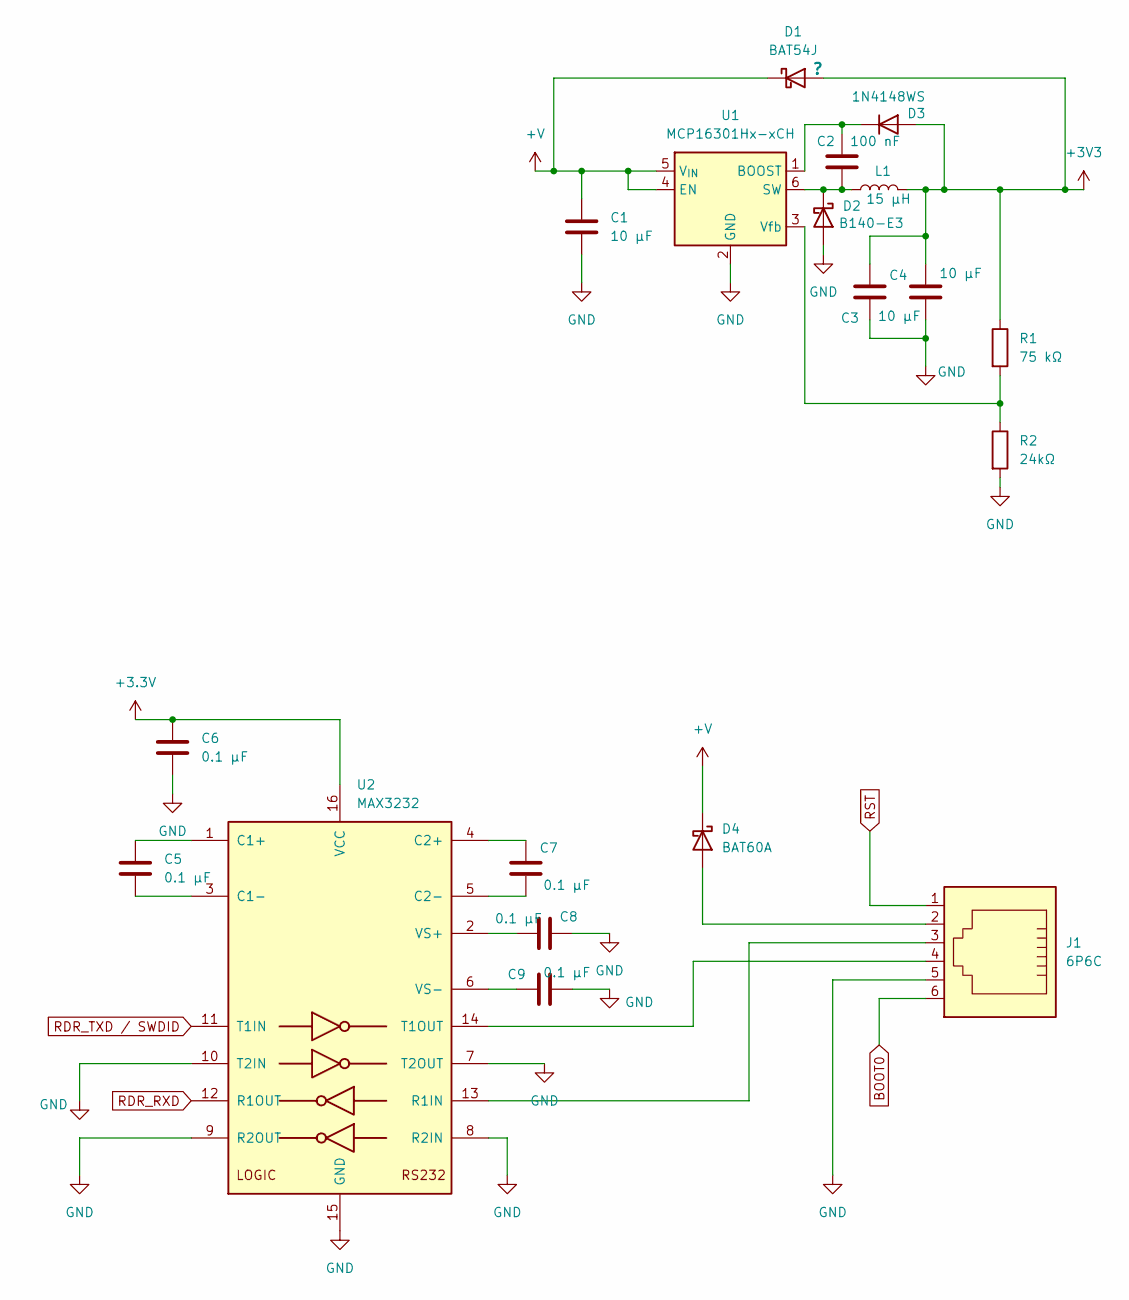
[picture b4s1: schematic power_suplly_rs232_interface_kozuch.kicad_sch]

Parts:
C1, C3, C4: 10 µF; C_0805_2012Metric
C2: 100 nF; C_0603_1608Metric
C5, C6, C7, C8, C9: 0.1 µF; C_0603_1608Metric
D1: BAT54J; D_SOD-323F
D2: B140-E3; D_SMA
D3: 1N4148WS; D_SOD-323
D4: BAT60A; D_SOD-323
J1: 6P6C; RJ12_Amphenol_54601-x06_Horizontal
L1: 15 µH; L_Coilcraft_LPS3010
R1: 75 kΩ; R_0603_1608Metric
R2: 24kΩ; R_0603_1608Metric
U1: MCP16301Hx-xCH; SOT-23-6
U2: MAX3232; SOIC-16W_7.5x12.8mm_P1.27mm

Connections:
+3.3V: C6.1, U2.16 (VCC)
+3V3: C3.1, C4.1, D1.2 (A), D3.2 (A), L1.2, R1.1
+V: C1.1, D1.1 (K), D4.1 (K), U1.4 (EN), U1.5 (V_{IN})
BOOT0: J1.6
GND: C1.2, C3.2, C4.2, C6.2, C8.2, C9.2, D2.2 (A), J1.5, R2.2, U1.2 (GND), U2.7 (T2OUT), U2.8 (R2IN), U2.9 (R2OUT), U2.10 (T2IN), U2.15 (GND)
unnamed: C2.2, D2.1 (K), L1.1, U1.6 (SW)
unnamed: C2.1, D3.1 (K), U1.1 (BOOST)
unnamed: D4.2 (A), J1.2
unnamed: R1.2, R2.1, U1.3 (Vfb)
unnamed: C5.1, U2.1 (C1+)
unnamed: C5.2, U2.3 (C1-)
unnamed: C7.1, U2.4 (C2+)
unnamed: C7.2, U2.5 (C2-)
unnamed: J1.3, U2.13 (R1IN)
unnamed: J1.4, U2.14 (T1OUT)
unnamed: C8.1, U2.2 (VS+)
unnamed: C9.1, U2.6 (VS-)
RDR_RXD: U2.12 (R1OUT)
RDR_TXD / SWDID: U2.11 (T1IN)
RST: J1.1

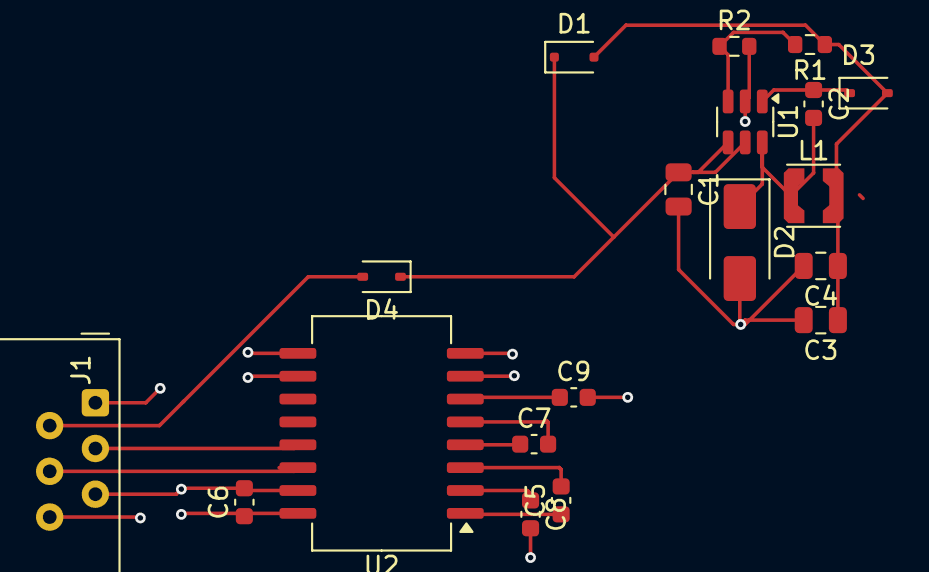
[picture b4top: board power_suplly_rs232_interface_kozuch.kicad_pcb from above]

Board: 2 copper layers, 19 parts (0 on the bottom side), 16 nets.

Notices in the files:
V2/kicad/reader.kicad_pcb:
CC BY NC SA
parts and their libraries:
CC BY-NC-SA 4.0
https://creativecommons.org/licenses/by-nc-sa/4.0
